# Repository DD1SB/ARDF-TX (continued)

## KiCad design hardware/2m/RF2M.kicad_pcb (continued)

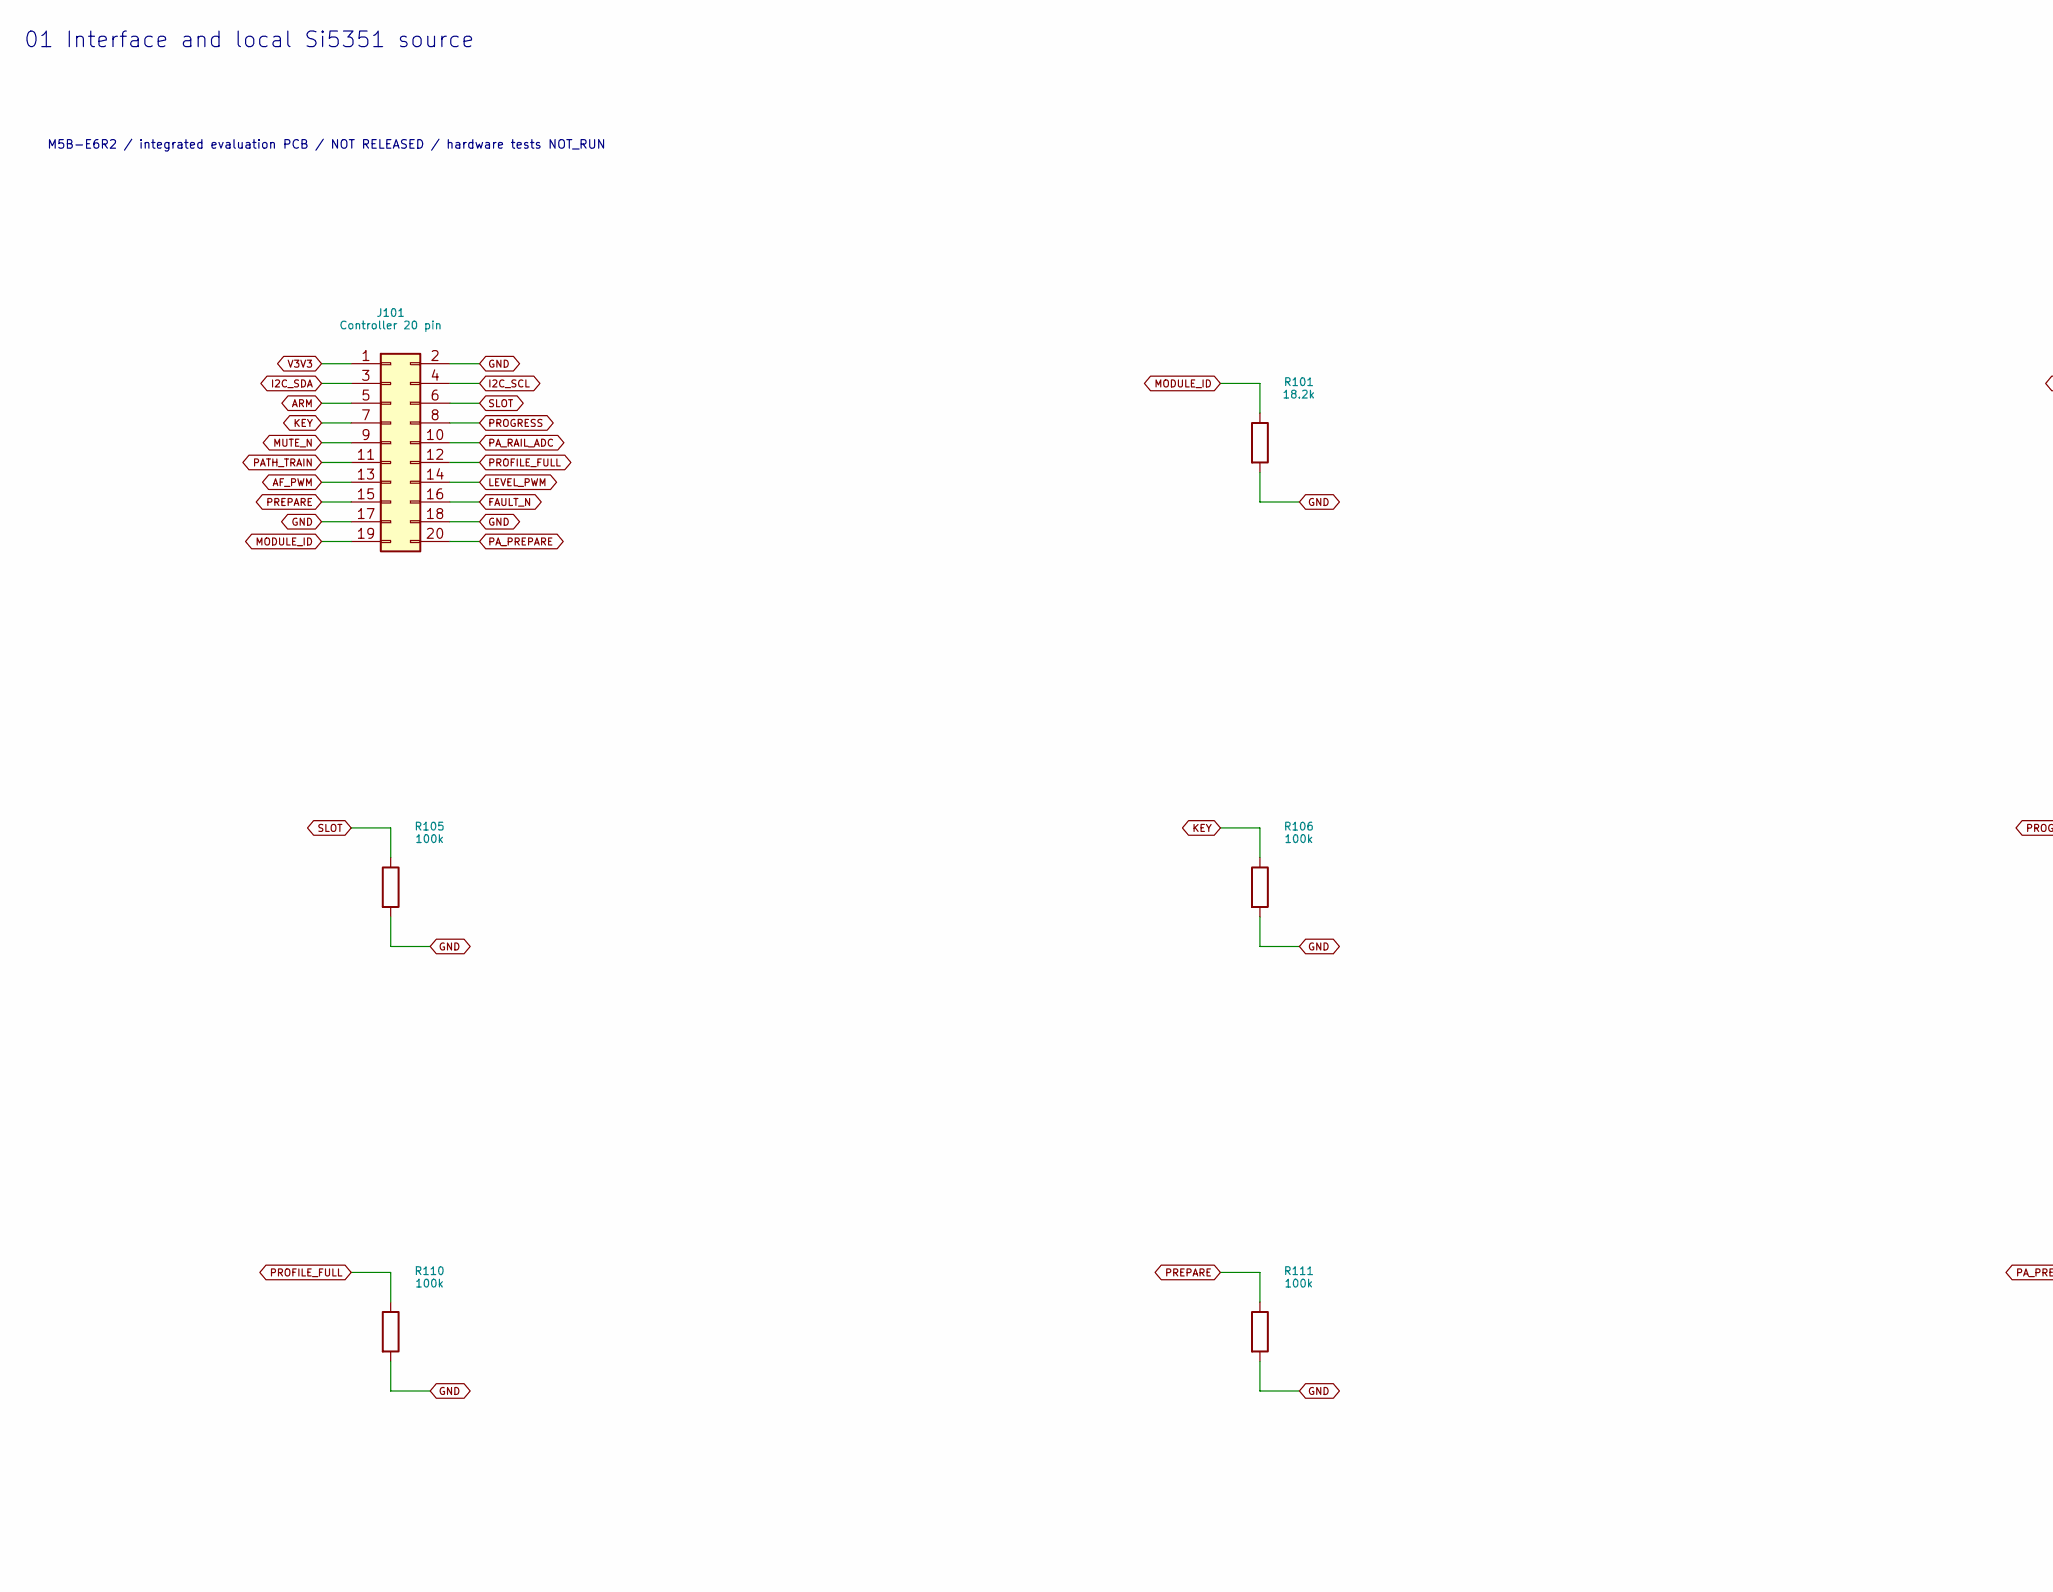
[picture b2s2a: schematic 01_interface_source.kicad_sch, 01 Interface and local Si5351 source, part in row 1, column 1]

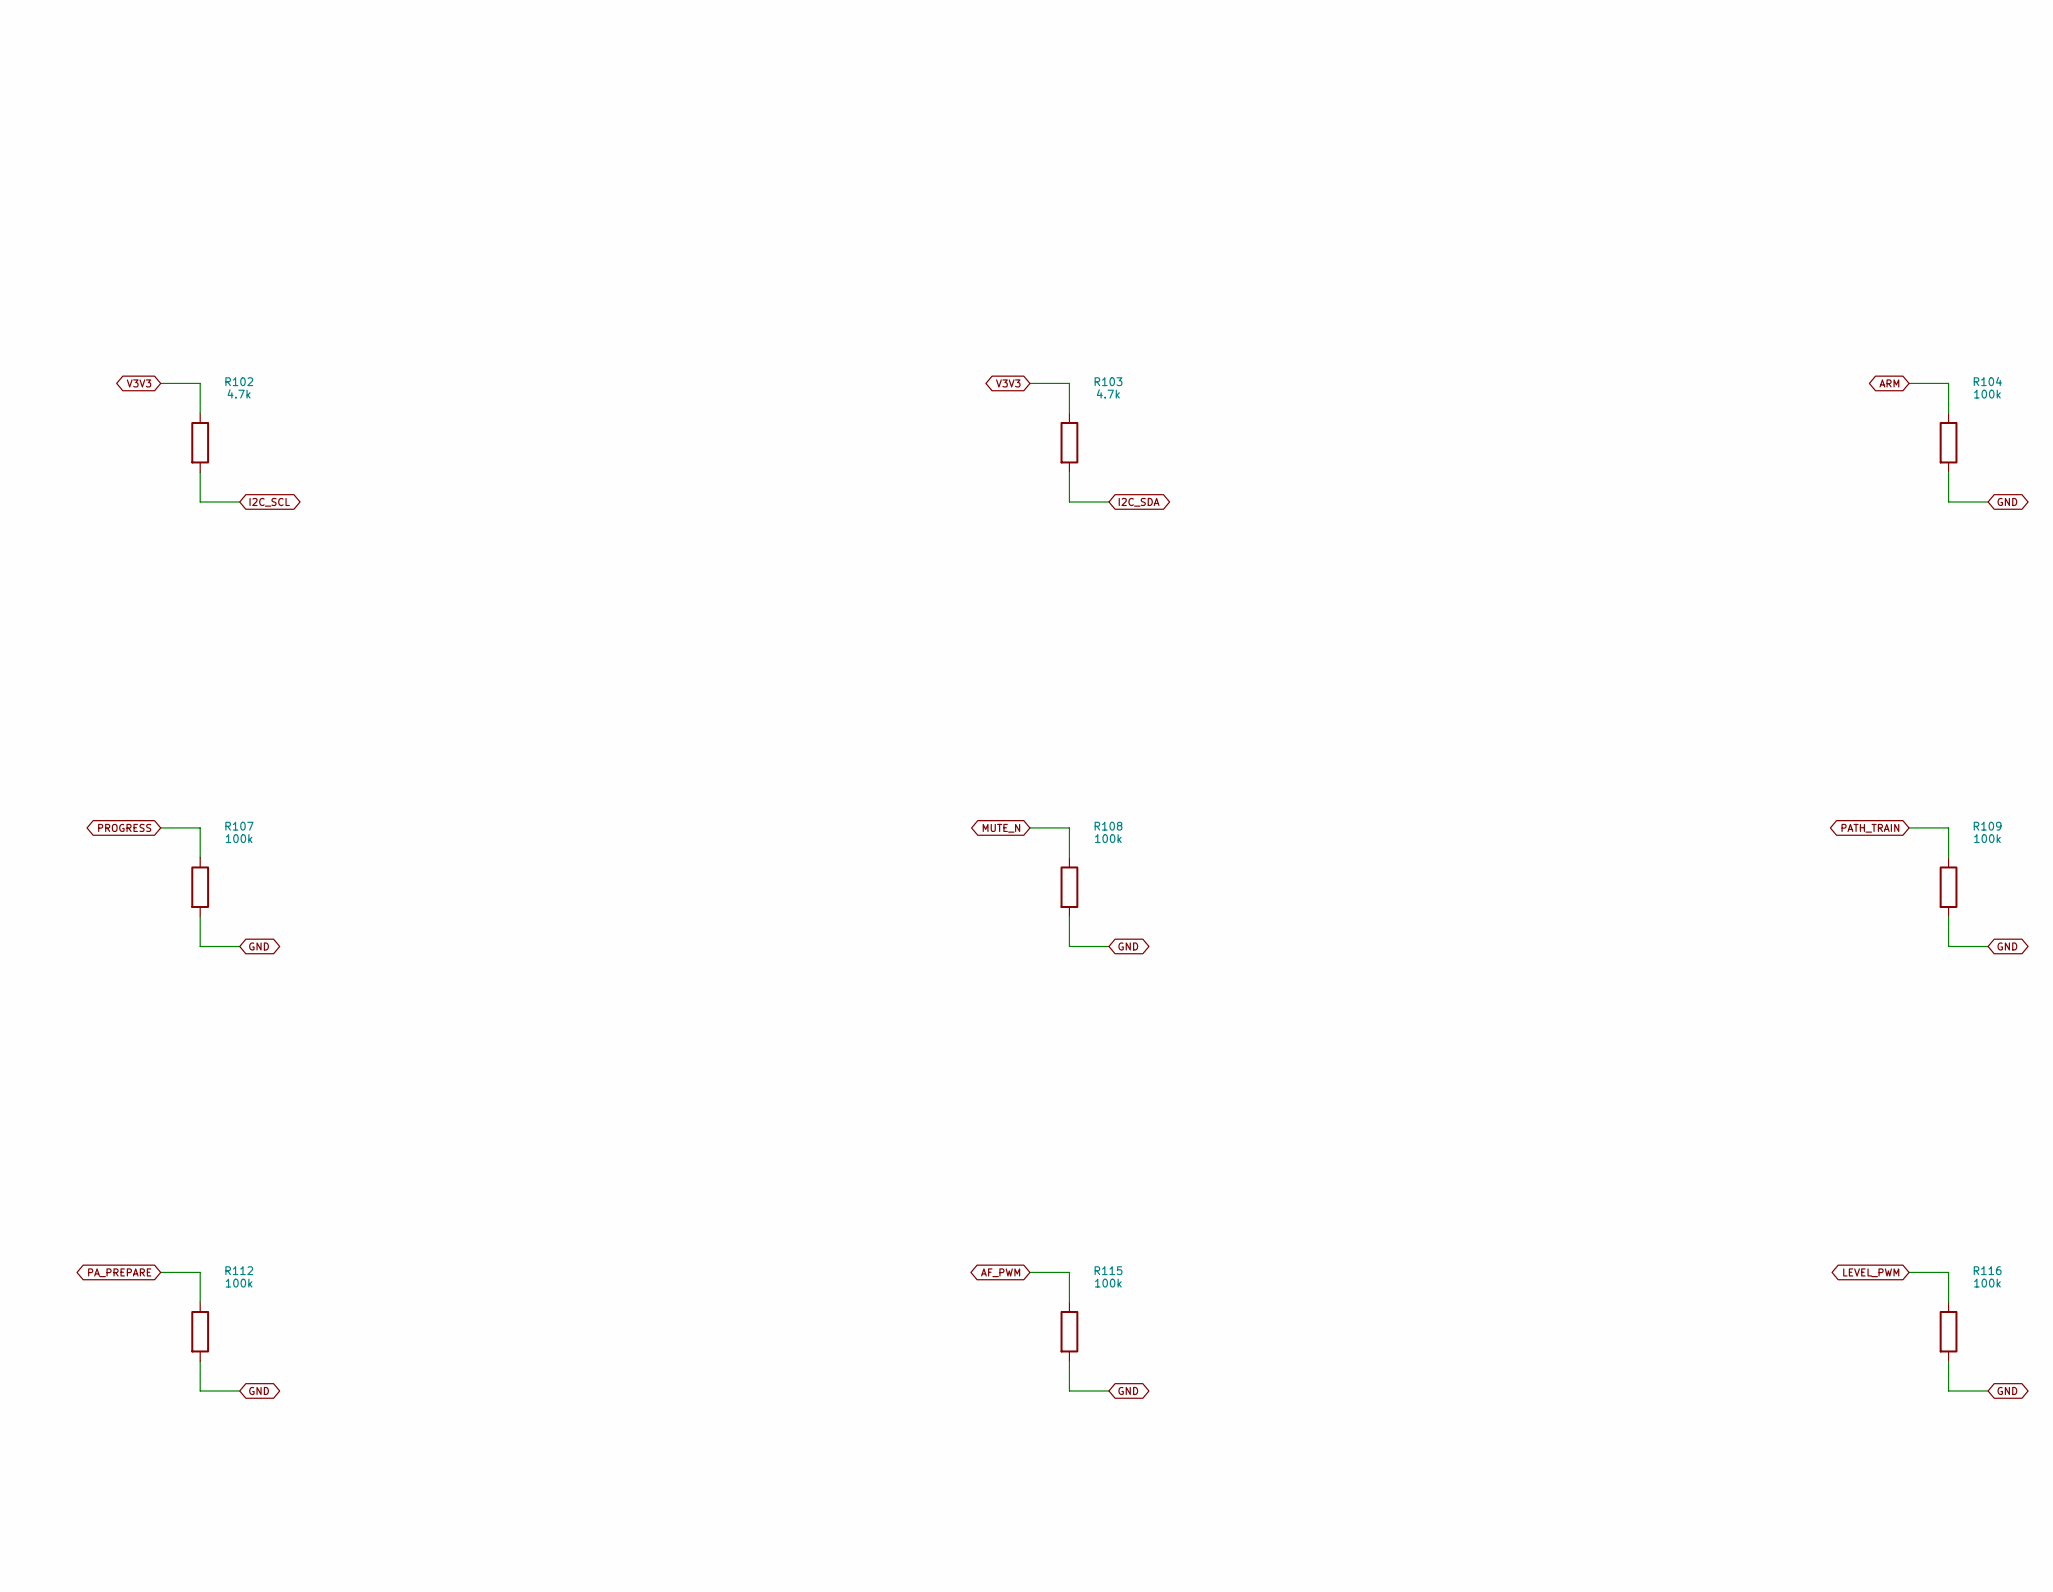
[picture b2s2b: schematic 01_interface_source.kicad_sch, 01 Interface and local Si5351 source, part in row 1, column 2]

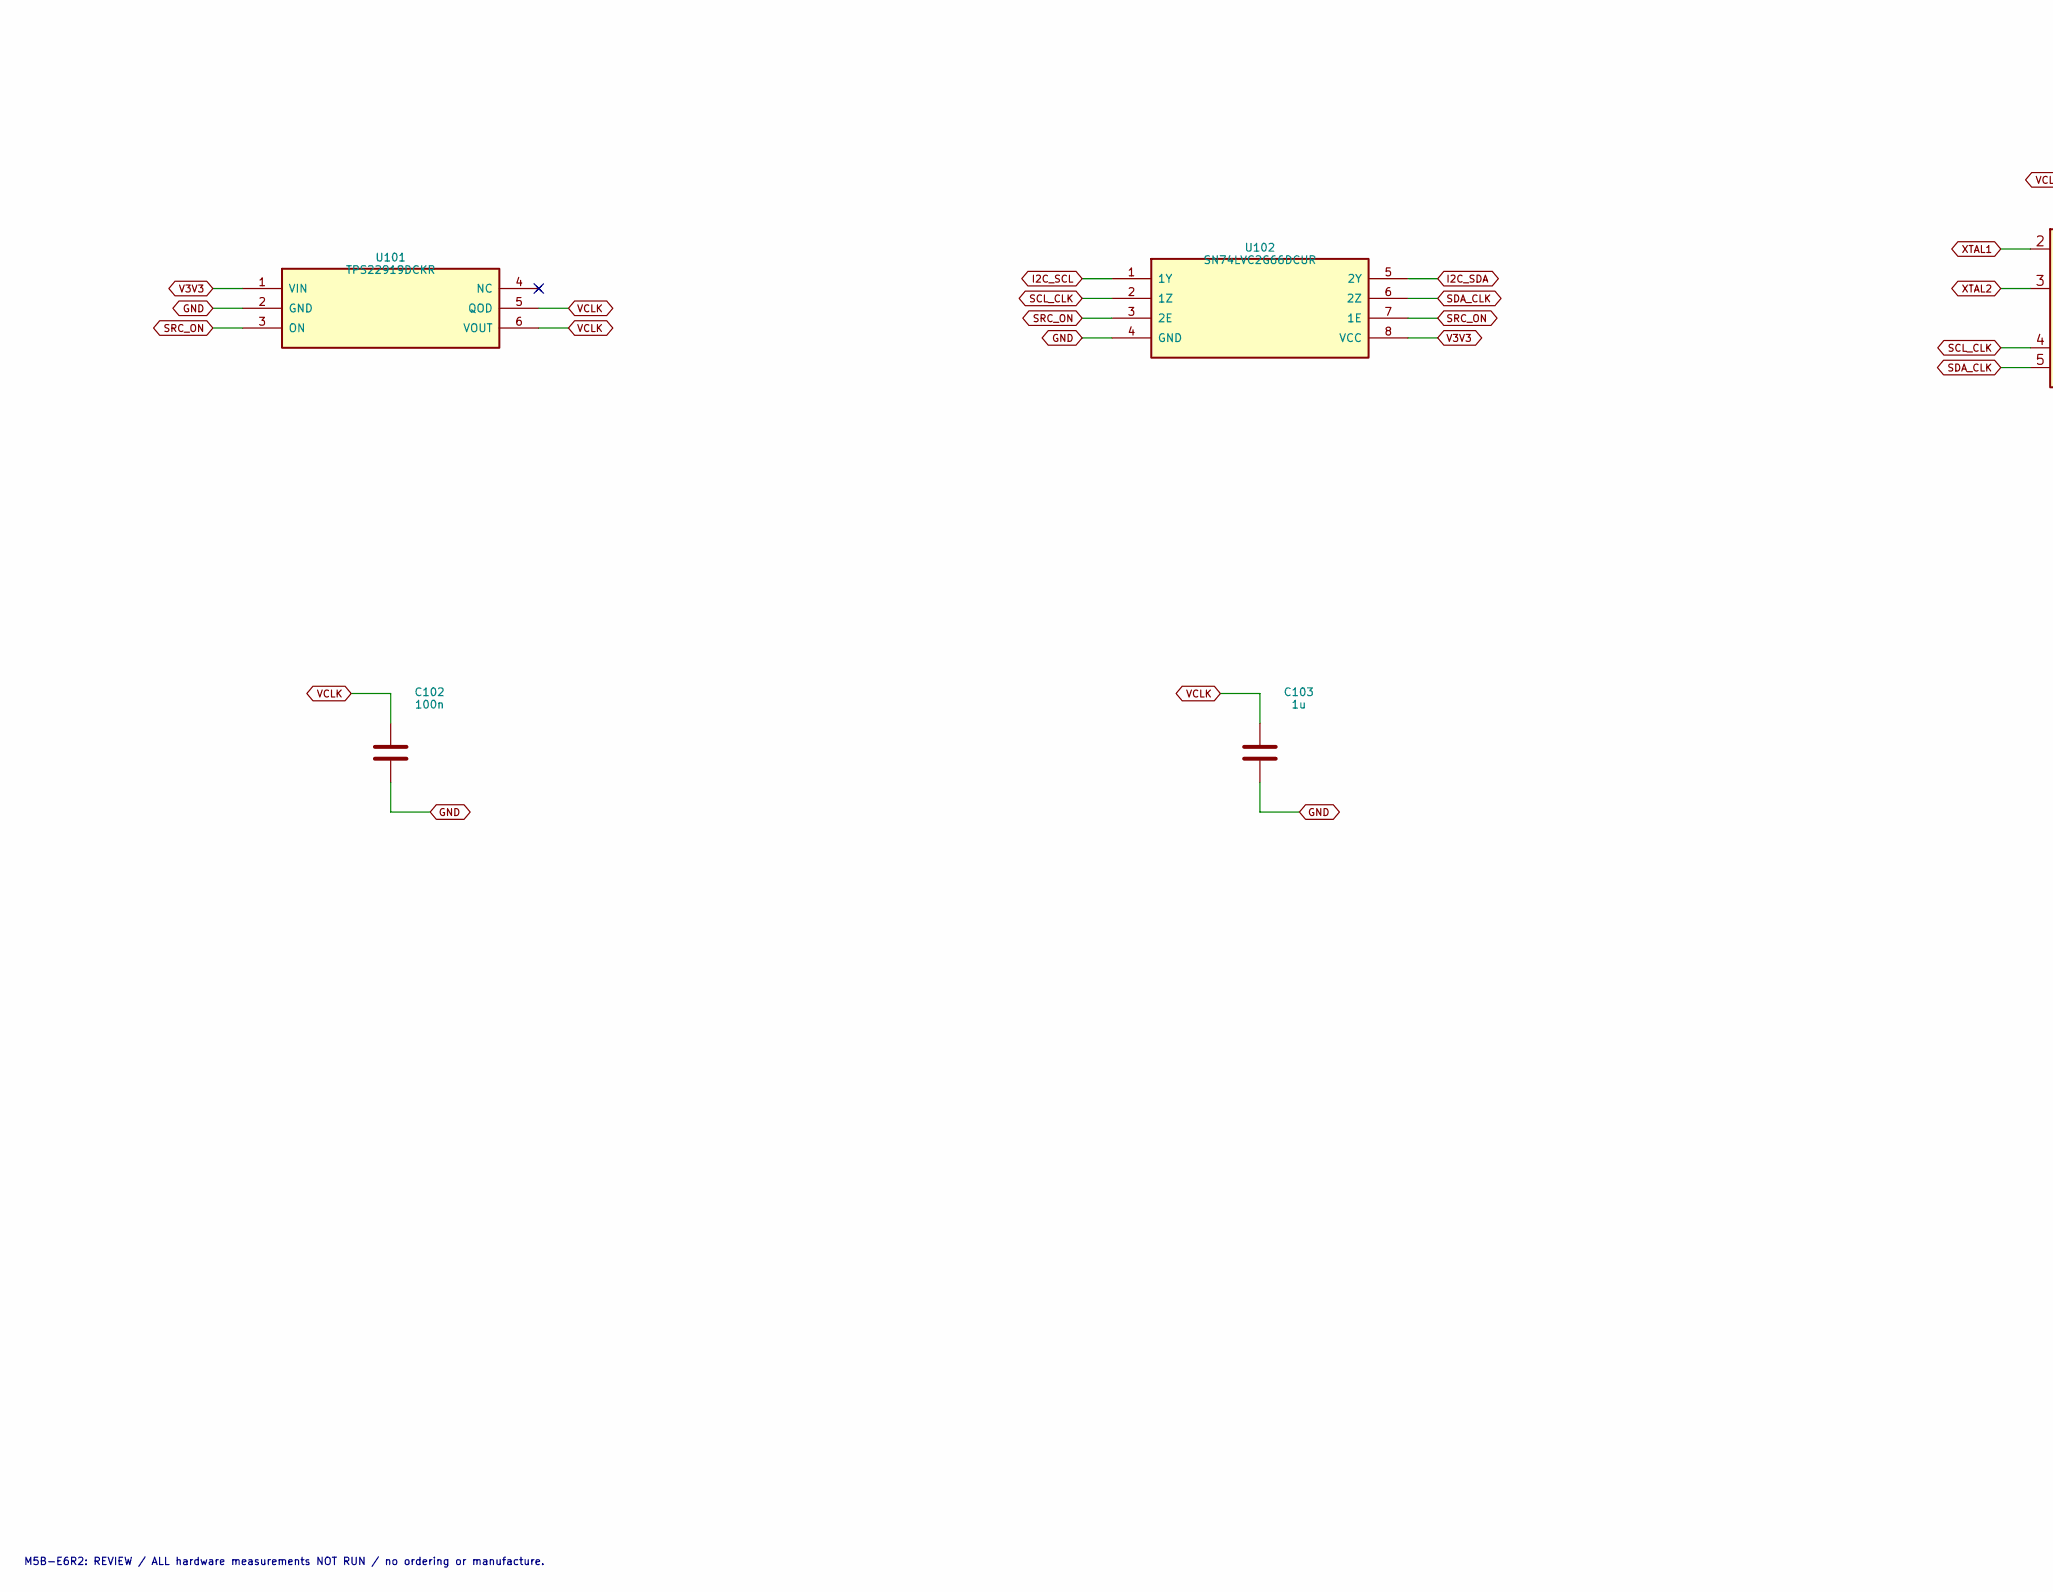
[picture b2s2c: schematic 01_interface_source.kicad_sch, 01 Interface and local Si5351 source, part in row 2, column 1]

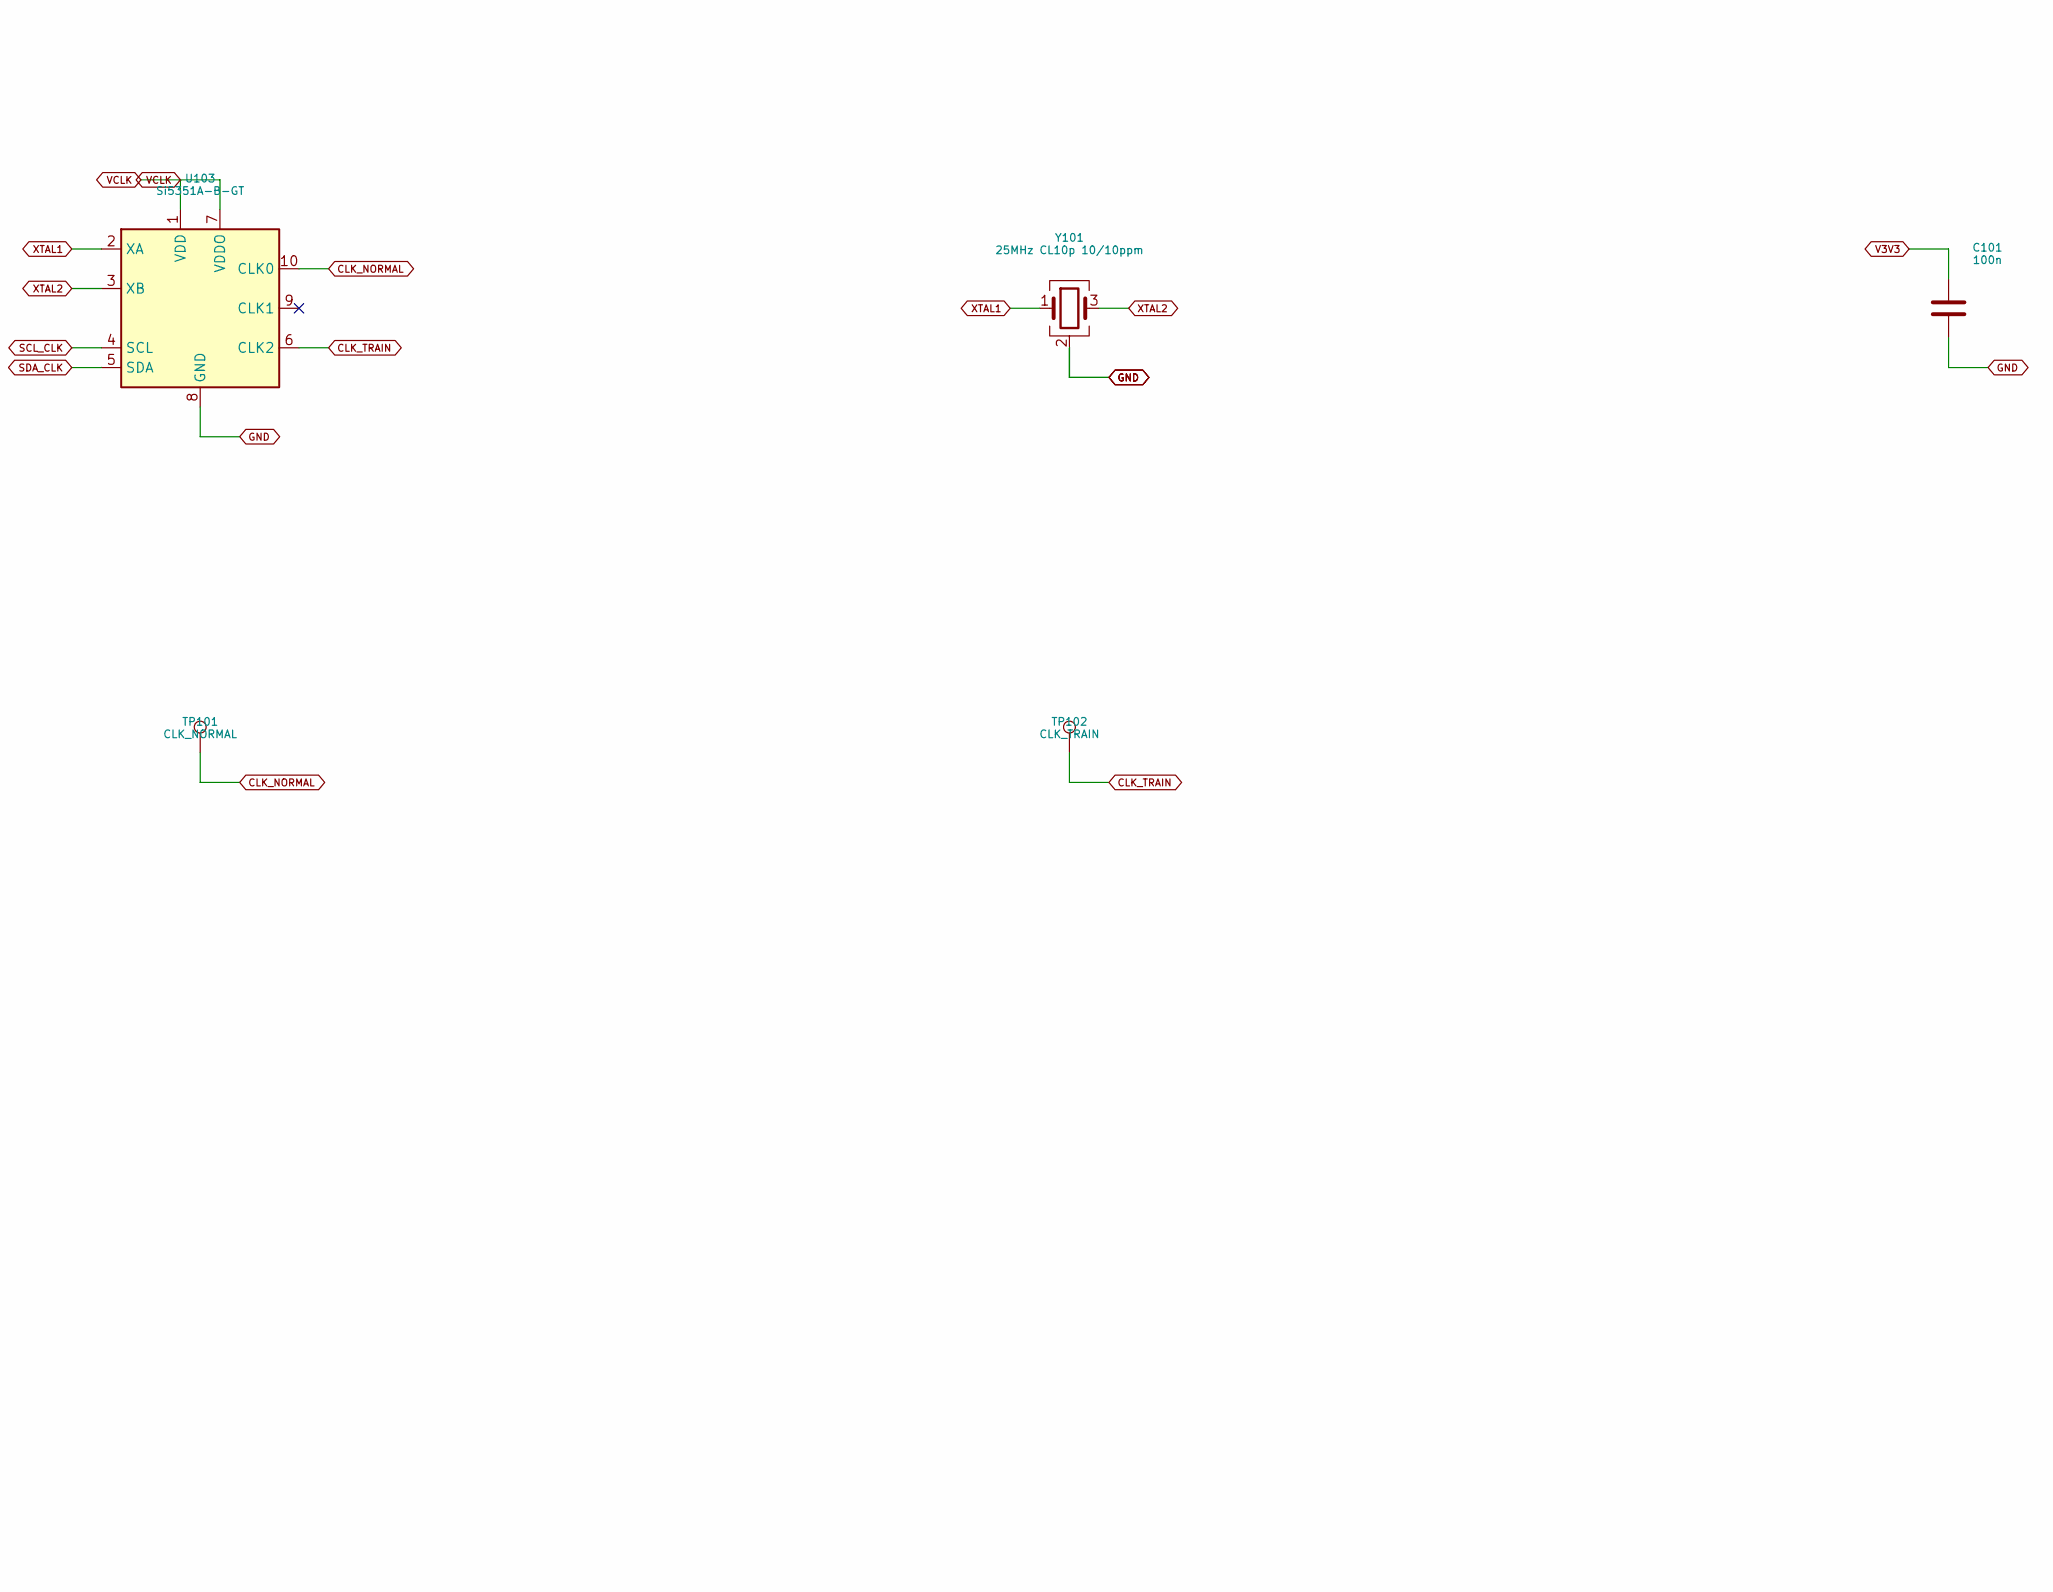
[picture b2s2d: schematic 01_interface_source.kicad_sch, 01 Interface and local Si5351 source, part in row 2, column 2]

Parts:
C101, C102: 100n; C_0603_1608Metric_E3; MPN CC0603KRX7R8BB104
C103: 1u; C_0805_2012Metric_E3; MPN CC0805KKX7R9BB105
J101: Controller 20 pin; WR_BHD_61202021621; MPN 61202021621
R101: 18.2k; R_0603_1608Metric_E3; MPN RC0603FR-0718K2L
R102, R103: 4.7k; R_0603_1608Metric_E3; MPN RC0603FR-074K7L
R104, R105, R106, R107, R108, R109, R110, R111, R112, R115, R116: 100k; R_0603_1608Metric_E3; MPN RC0603FR-07100KL
TP101: CLK_NORMAL; TestPoint_Pad_D1.0mm_E3; MPN PCB feature
TP102: CLK_TRAIN; TestPoint_Pad_D1.0mm_E3; MPN PCB feature
U101: TPS22919DCKR; SOT-363_SC-70-6_E3; MPN TPS22919DCKR
U102: SN74LVC2G66DCUR; VSSOP-8_2.3x2mm_P0.5mm_E3; MPN SN74LVC2G66DCUR
U103: Si5351A-B-GT; MSOP-10_3x3mm_P0.5mm_E3; MPN Si5351A-B-GT
Y101: 25MHz CL10p 10/10ppm; Crystal_SMD_3225-4Pin_3.2x2.5mm_E3; MPN ABM8-25.000MHZ-10-B1U-T

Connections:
AF_PWM: J101.13, R115.1; also elsewhere on the board
ARM: J101.5, R104.1; also elsewhere on the board
CLK_NORMAL: TP101.1, U103.10 (CLK0); also elsewhere on the board
CLK_TRAIN: TP102.1, U103.6 (CLK2); also elsewhere on the board
FAULT_N: J101.16; also elsewhere on the board
GND: C101.2, C102.2, C103.2, J101.2, J101.17, J101.18, R101.2, R104.2, R105.2, R106.2, R107.2, R108.2, R109.2, R110.2, R111.2, R112.2, R115.2, R116.2, U101.2 (GND), U102.4 (GND), U103.8 (GND), Y101.2 (G), Y101.4 (G); also elsewhere on the board
I2C_SCL: J101.4, R102.2, U102.1 (1Y); also elsewhere on the board
I2C_SDA: J101.3, R103.2, U102.5 (2Y)
KEY: J101.7, R106.1; also elsewhere on the board
LEVEL_PWM: J101.14, R116.1; also elsewhere on the board
MODULE_ID: J101.19, R101.1
MUTE_N: J101.9, R108.1; also elsewhere on the board
PATH_TRAIN: J101.11, R109.1; also elsewhere on the board
PA_PREPARE: J101.20, R112.1; also elsewhere on the board
PA_RAIL_ADC: J101.10; also elsewhere on the board
PREPARE: J101.15, R111.1; also elsewhere on the board
PROFILE_FULL: J101.12, R110.1; also elsewhere on the board
PROGRESS: J101.8, R107.1; also elsewhere on the board
SCL_CLK: U102.2 (1Z), U103.4 (SCL)
SDA_CLK: U102.6 (2Z), U103.5 (SDA)
SLOT: J101.6, R105.1; also elsewhere on the board
SRC_ON: U101.3 (ON), U102.3 (2E), U102.7 (1E); also elsewhere on the board
V3V3: C101.1, J101.1, R102.1, R103.1, U101.1 (VIN), U102.8 (VCC); also elsewhere on the board
VCLK: C102.1, C103.1, U101.5 (QOD), U101.6 (VOUT), U103.1 (VDD), U103.7 (VDDO)
XTAL1: U103.2 (XA), Y101.1
XTAL2: U103.3 (XB), Y101.3

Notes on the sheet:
01 Interface and local Si5351 source
M5B-E6R2 / integrated evaluation PCB / NOT RELEASED / hardware tests NOT_RUN
M5B-E6R2: REVIEW / ALL hardware measurements NOT RUN / no ordering or manufacture.
